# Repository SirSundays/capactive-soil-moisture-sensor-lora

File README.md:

# Capactive Soil Moisture Sensor with LoRa

This sensor is a capacitive soil moisture sensor with a completely 3D printable housing, which can send its data over LoRaWAN into the IoT.

## Short Description

Are you interested in a soil moisture and temperature sensor that is suitable for plant pots? If so, you might want to check out my project: the “All in One Capacitive Soil Moisture Sensor w/ LoRa”. This project combines capacitive sensing, LoRaWAN, and 3D printing technologies to create a simple, compact, and efficient sensor. It has a single PCB that serves as both the sensing element and the electronic circuit. A Heltec CubeCell module provides low-power LoRaWAN connectivity to an IoT network. The sensor also measures the actual soil temperature and calibrates the moisture readings for different soil types. A layer of epoxy protects the sensor from various environmental conditions and a rotary device helps to apply it evenly. The sensor is easy to install and use, as it only requires to be inserted into the soil. It also has a good battery life, lasting for several months without replacement.

If you want to know more about the project you can read a full explanation on hackaday: [All in One Capacitive Soil Moisture Sensor w/ LoRa](https://hackaday.io/project/194052-all-in-one-capactive-soil-moisture-sensor-w-lora)

## Files
| File Path  | Description  |
| ------------- |--------------  |
|       | 3D-Data for an epoxy potting jig for the lower half of the housing and a turning device for evenly curing the epoxy when applied to the sensor and housing      |
|       | 3D-Data for a simple programming jig to easily program and debug the sensor node      |
|      | 3D-Data for both the standard sensor housing, as well as a split housing with a hole for antenna matching      |
|  | All Files developed and used to find the optimal values for the circuit parameters for example generated frequency and capacitor and resistor values |
|  | Developed code for the Heltec CubeCell AM01 V2. Used with Arduino IDE, Heltec Boards installed. Also depends on OneWire and DallasTemperature library. |
|  | TheThingsNetwork JavaScript Payload decoder to decode the data. |
|  | All important photos and videos I took while developing and testing the sensor. Just gives an inside on how some of the stuff works (or did not work). |
|  | Small PCB, to test out the principle of the temperature chip sensor being flipped so it sits inside the PCB. The uploaded version was the one that worked the best.
|  | Final PCB including Gerber Files for ordering at JLCPCB |
|  | Grove Capactive Soil Moisture Sensor heavily modified to only include the main PCB trace and no electronics, except a header in the top to be able to connect it to a breadboard.

## License
The hardware and associated design files are released under the Creative Commons CC BY-SA 4.0 license. The code is released under the MIT license.

Projects that inspired this project and which partly got worked into this project are:
- 
- 

## Disclaimer
This product is not officially LoRaWAN or LoRa certified through the LoRa Alliance. LoRa and LoRaWAN are trademarks of the LoRa Alliance. Heltec states that the module is compatible with the LoRaWAN standard V 1.0.2, but I did not do any verification in that regard.

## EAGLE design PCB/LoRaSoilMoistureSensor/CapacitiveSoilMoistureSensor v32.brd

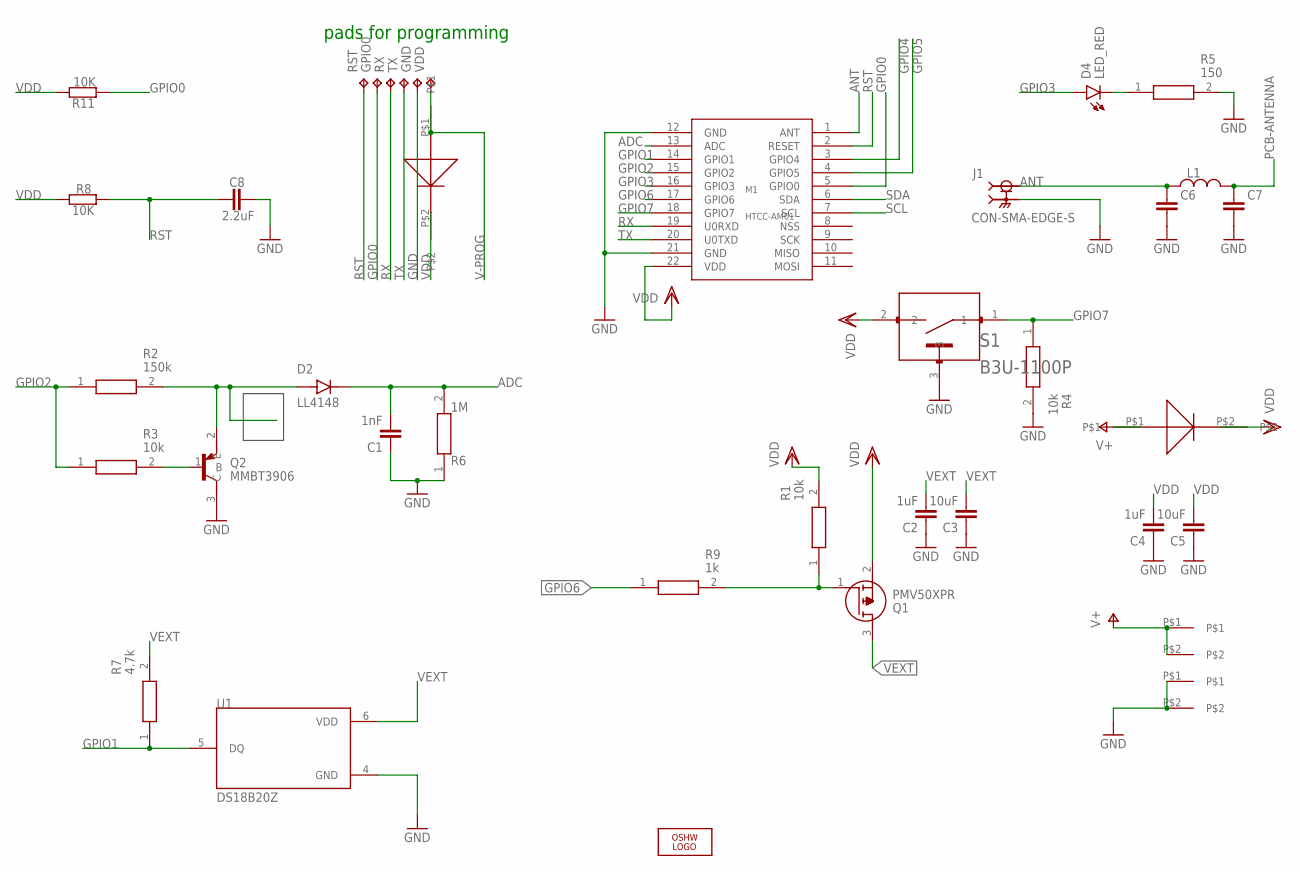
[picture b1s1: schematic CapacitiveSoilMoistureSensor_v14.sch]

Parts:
C1: 1nF; C0603
C2, C4: 1uF; C0603
C3, C5: 10uF; C0603
C6, C7: C_CHIP-0603(1608-METRIC); CAPC1608X85
C8: 2.2uF; C0603
D1, D3: SOD-323
D2: LL4148; DIO_LL4148
D4: LED_RED; LEDC1608X80N_FLAT-R
GND: TPTP20SQ; TP20SQ
GPIO0: TPTP20SQ; TP20SQ
J1: CON-SMA-EDGE-S; RFSOLUTIONS_CON-SMA-EDGE-S
L1: L_CHIP-0603(1608-METRIC); INDC1608X95N
LOGO1: LOGO-OSHW-FILLX0200-NT; OSHW_FILLX200_NOTEXT
M1: HTCC-AM01
Q1: PMV50XPR; SOT95P230X110-3N
Q2: MMBT3906; SOT95P240X120-3N
R1, R3, R4: 10k; RESC1608X55N
R2: 150k; RESC1608X55N
R5: 150; RESC1608X55N
R6: 1M; RESC1608X55N
R7: 4.7k; RESC1608X55N
R8, R11: 10K; R0603
R9: 1k; RESC1608X55N
RST: TPTP20SQ; TP20SQ
RX: TPTP20SQ; TP20SQ
S1: B3U-1100P; SW_B3U-1100P
TX: TPTP20SQ; TP20SQ
U1: DS18B20Z; SOIC127P600X175-8N
U$3, U$4: KEYSTONE53
VDD: TPTP20SQ; TP20SQ

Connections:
ADC: C1.2, D2.C, M1.13 (ADC), R6.2
ANT: C6.1, J1.1, L1.1, M1.1 (ANT)
GND: C1.1, C2.1, C3.1, C4.1, C5.1, C6.2, C7.2, C8.1, GND.TP, J1.G1 (2), J1.G2 (2), J1.G3 (2), J1.G4 (2), M1.12 (GND), M1.21 (GND), Q2.3 (C), R4.2, R5.2, R6.1, S1.3, U1.4 (GND), U$4.P$1, U$4.P$2
GPIO0: GPIO0.TP, M1.5 (GPIO0), R11.2
GPIO1: M1.14 (GPIO1), R7.1, U1.5 (DQ)
GPIO2: M1.15 (GPIO2), R2.1, R3.1
GPIO3: D4.A, M1.16 (GPIO3)
GPIO4: M1.3 (GPIO4)
GPIO5: M1.4 (GPIO5)
GPIO6: M1.17 (GPIO6), R9.1
GPIO7: M1.18 (GPIO7), R4.1, S1.1
unnamed: Q1.1 (G), R1.1, R9.2
unnamed: Q2.1 (B), R3.2
unnamed: D4.C, R5.1
unnamed: D2.A, Q2.2 (E), R2.2
PCB-ANTENNA: C7.1, L1.2
RST: C8.2, M1.2 (RESET), R8.2, RST.TP
RX: M1.19 (U0RXD), RX.TP
SCL: M1.7 (SCL)
SDA: M1.6 (SDA)
TX: M1.20 (U0TXD), TX.TP
V+: D1.P$1, U$3.P$1, U$3.P$2
V-PROG: D3.P$1, VDD.TP
VDD: C4.2, C5.2, D1.P$2, D3.P$2, M1.22 (VDD), Q1.2 (S), R1.2, R8.1, R11.1, S1.2
VEXT: C2.2, C3.2, Q1.3 (D), R7.2, U1.6 (VDD)

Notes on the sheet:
pads for programming

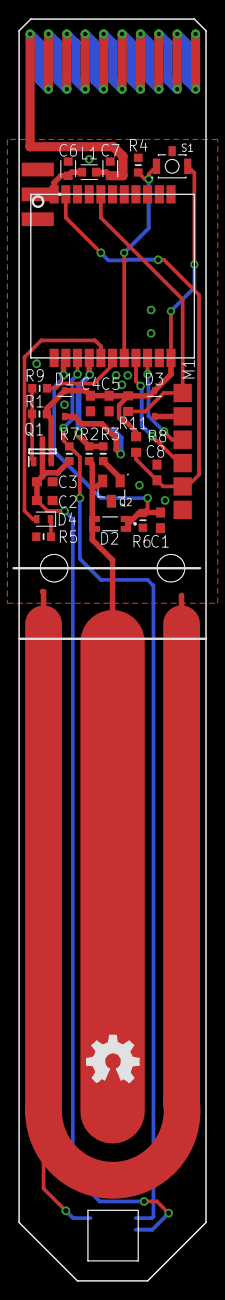
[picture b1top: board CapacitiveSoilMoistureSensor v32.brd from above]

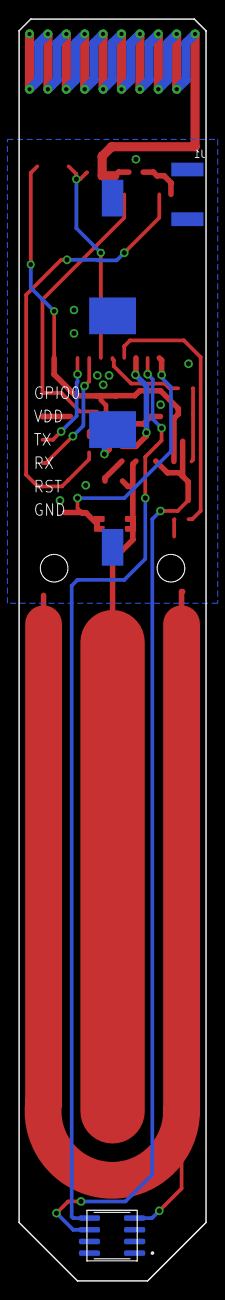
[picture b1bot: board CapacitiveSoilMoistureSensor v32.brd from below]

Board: 2 copper layers, 20.3 x 137.2 mm, 38 parts (3 on the bottom side), 21 nets.

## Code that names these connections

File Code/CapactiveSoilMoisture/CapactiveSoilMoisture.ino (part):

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#include <OneWire.h>
#include <DallasTemperature.h>

#define ONE_WIRE_BUS GPIO1

OneWire oneWire(ONE_WIRE_BUS);
DallasTemperature sensors(&oneWire);
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      uplinks++;
    }

    digitalWrite(GPIO6, LOW);
    delay(10);

    sensors.begin();
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
    uint16_t temp100 = temperature * 100;

    digitalWrite(GPIO6, HIGH);

    // Read Soil Moisture
    pwmEnable();
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  deviceState = DEVICE_STATE_INIT;
  LoRaWAN.ifskipjoin();

  pinMode(GPIO6, OUTPUT);
  digitalWrite(GPIO6, LOW);
  delay(20);

  sensors.begin();
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  if (sensors.getTempCByIndex(0) != -127) {
    setupErrorDS = true;
  }
  digitalWrite(GPIO6, HIGH);

  pinMode(GPIO0, ANALOG);
  pinMode(GPIO3, ANALOG);
  pinMode(GPIO4, ANALOG);
  pinMode(GPIO5, ANALOG);

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
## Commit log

2024-01-25 Add files via upload
    Adding all project files
2024-02-11 Create README.md for sub folder CapTest
